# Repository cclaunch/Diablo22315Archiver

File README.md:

Diablo disk drive model 31, in its standard density version, can read or write to the 2315 disk cartridges interchanngeably with the disk drives in the IBM 1130 system 

This project exploits an FPGA board with a custom interface board to control the Diablo disk drive. It will read the contents of the disk cartridge into RAM on the FPGA board. 

It then uploads the contents over the USB serial link so that the contents can be archived. The software will take the data streaming over the USB link and create disk files 
in the format used with the IBM 1130 simulator programs (and therefore with the Virtual 2315 Cartridge Facility to access them on a real 1130 system. 

The PCB connects to the FPGA board, provides power to the FPGA and the logic on the PCB, and connects to the Diablo disk drive using an IDC 50 pin cable.

A PCB is available to create the Head Adapter Tool used in aligning a Diablo 31 standard density drive using the CE Cartridge

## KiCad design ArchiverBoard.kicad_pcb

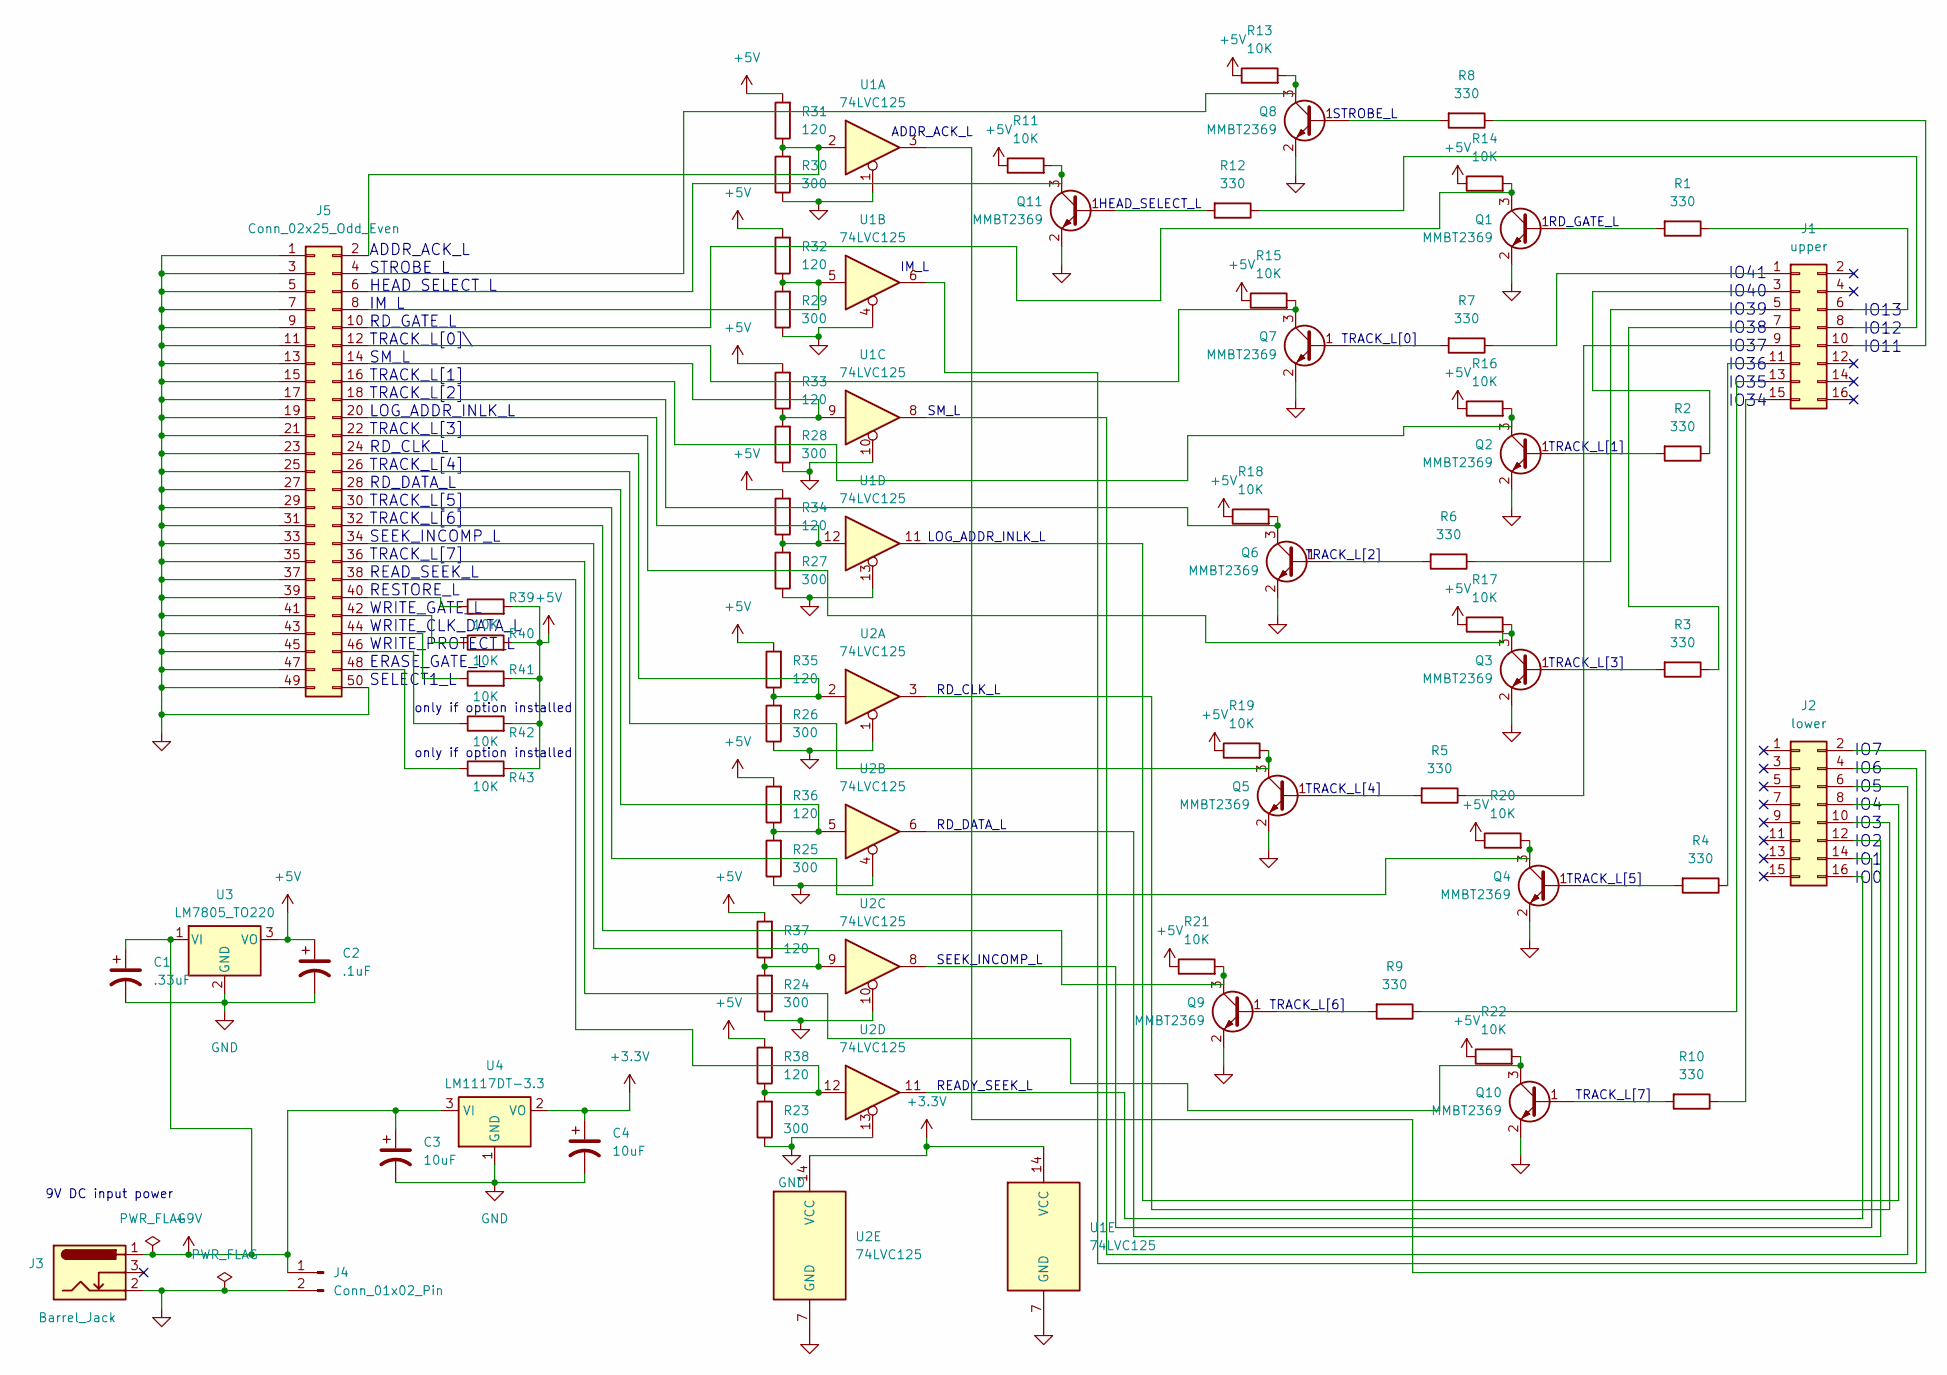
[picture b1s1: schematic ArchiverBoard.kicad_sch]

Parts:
C1: .33uF; C_0805_2012Metric
C2: .1uF; C_1206_3216Metric
C3, C4: 10uF; C_1206_3216Metric
J1: upper; PinHeader_2x08_P2.54mm_Vertical
J2: lower; PinHeader_2x08_P2.54mm_Vertical
J3: Barrel_Jack; BarrelJack_Kycon_KLDX-0202-xC_Horizontal
J4: Conn_01x02_Pin; PinHeader_1x02_P2.54mm_Vertical
J5: Conn_02x25_Odd_Even; IDC-Header_2x25_P2.54mm_Vertical
Q1, Q2, Q3, Q4, Q5, Q6, Q7, Q8, Q9, Q10, Q11: MMBT2369; SOT-23
R1, R2, R3, R4, R5, R6, R7, R8, R9, R10, R12: 330; R_0603_1608Metric
R11, R13, R14, R15, R16, R17, R18, R19, R20, R21, R22, R39, R40, R41, R42, R43: 10K; R_0603_1608Metric
R23, R24, R25, R26, R27, R28, R29, R30: 300; R_0603_1608Metric
R31, R32, R33, R34, R35, R36, R37, R38: 120; R_0603_1608Metric
U1, U2: 74LVC125; SO-14_3.9x8.65mm_P1.27mm
U3: LM7805_TO220; TO-220-3_Vertical
U4: LM1117DT-3.3; SOT-223

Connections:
+3.3V: C4.1, U1.14 (VCC), U2.14 (VCC), U4.2 (VO), U4.4
+5V: C2.1, R11.1, R13.1, R14.1, R15.1, R16.1, R17.1, R18.1, R19.1, R20.1, R21.1, R22.1, R31.2, R32.2, R33.2, R34.2, R35.2, R36.2, R37.2, R38.2, R39.2, R40.2, R41.2, R42.2, R43.2, U3.3 (VO)
+9V: C1.1, C3.1, J3.1, J4.1, U3.1 (VI), U4.3 (VI)
GND: C1.2, C2.2, C3.2, C4.2, J3.2, J4.2, J5.1, J5.3, J5.5, J5.7, J5.9, J5.11, J5.13, J5.15, J5.17, J5.19, J5.21, J5.23, J5.25, J5.27, J5.29, J5.31, J5.33, J5.35, J5.37, J5.39, J5.41, J5.43, J5.45, J5.47, J5.49, J5.50, Q1.2 (E), Q2.2 (E), Q3.2 (E), Q4.2 (E), Q5.2 (E), Q6.2 (E), Q7.2 (E), Q8.2 (E), Q9.2 (E), Q10.2 (E), Q11.2 (E), R23.1, R24.1, R25.1, R26.1, R27.1, R28.1, R29.1, R30.1, U1.1, U1.4, U1.7 (GND), U1.10, U1.13, U2.1, U2.4, U2.7 (GND), U2.10, U2.13, U3.2 (GND), U4.1 (GND)
unnamed: J1.1, R7.1
unnamed: J1.3, R2.1
unnamed: J1.5, R6.1
unnamed: J1.6, R1.1
unnamed: J1.7, R3.1
unnamed: J1.8, R12.1
unnamed: J1.9, R5.1
unnamed: J1.10, R8.1
unnamed: J1.11, R4.1
unnamed: J1.13, R9.1
unnamed: J1.15, R10.1
unnamed: J2.2, U1.3
unnamed: J2.4, U1.6
unnamed: J2.6, U1.8
unnamed: J2.8, U1.11
unnamed: J2.10, U2.3
unnamed: J2.12, U2.6
unnamed: J2.14, U2.8
unnamed: J2.16, U2.11
unnamed: J5.2, R30.2, R31.1, U1.2
unnamed: J5.4, Q8.3 (C), R13.2
unnamed: J5.6, Q11.3 (C), R11.2
unnamed: J5.8, R29.2, R32.1, U1.5
unnamed: J5.10, Q1.3 (C), R14.2
unnamed: J5.12, Q7.3 (C), R15.2
unnamed: J5.14, R28.2, R33.1, U1.9
unnamed: J5.16, Q2.3 (C), R16.2
unnamed: J5.18, Q6.3 (C), R18.2
unnamed: J5.20, R27.2, R34.1, U1.12
unnamed: J5.22, Q3.3 (C), R17.2
unnamed: J5.24, R26.2, R35.1, U2.2
unnamed: J5.26, Q5.3 (C), R19.2
unnamed: J5.28, R25.2, R36.1, U2.5
unnamed: J5.30, Q4.3 (C), R20.2
unnamed: J5.32, Q9.3 (C), R21.2
unnamed: J5.34, R24.2, R37.1, U2.9
unnamed: J5.36, Q10.3 (C), R22.2
unnamed: J5.38, R23.2, R38.1, U2.12
unnamed: J5.40, R39.1
unnamed: J5.42, R40.1
unnamed: J5.44, R41.1
unnamed: J5.46, R42.1
unnamed: J5.48, R43.1
unnamed: Q1.1 (B), R1.2
unnamed: Q2.1 (B), R2.2
unnamed: Q3.1 (B), R3.2
unnamed: Q4.1 (B), R4.2
unnamed: Q5.1 (B), R5.2
unnamed: Q6.1 (B), R6.2
unnamed: Q7.1 (B), R7.2
unnamed: Q8.1 (B), R8.2
unnamed: Q9.1 (B), R9.2
unnamed: Q10.1 (B), R10.2
unnamed: Q11.1 (B), R12.2

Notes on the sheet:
RD_DATA_L
RD_GATE_L
9V DC input power
ADDR_ACK_L STROBE_L HEAD_SELECT_L IM_L RD_GATE_L TRACK_L[0]\ SM_L TRACK_L[1] TRACK_L[2] LOG_ADDR_INLK_L TRACK_L[3] RD_CLK_L TRACK_L[4] RD_DATA_L TRACK_L[5] TRACK_L[6] SEEK_INCOMP_L TRACK_L[7] READ_SEEK_L RESTORE_L WRITE_GATE_L WRITE_CLK_DATA_L WRITE_PROTECT_L ERASE_GATE_L SELECT1_L
IO41 IO40 IO39 IO38 IO37 IO36 IO35 IO34
TRACK_L[7]
ADDR_ACK_L
TRACK_L[2]
TRACK_L[1]
IO13 IO12 IO11
IO7 IO6 IO5 IO4 IO3 IO2 IO1 IO0
LOG_ADDR_INLK_L
TRACK_L[5]
TRACK_L[4]
TRACK_L[6]
READY_SEEK_L
TRACK_L[0]
STROBE_L
SEEK_INCOMP_L
only if option installed
IM_L
HEAD_SELECT_L
RD_CLK_L
TRACK_L[3]
SM_L

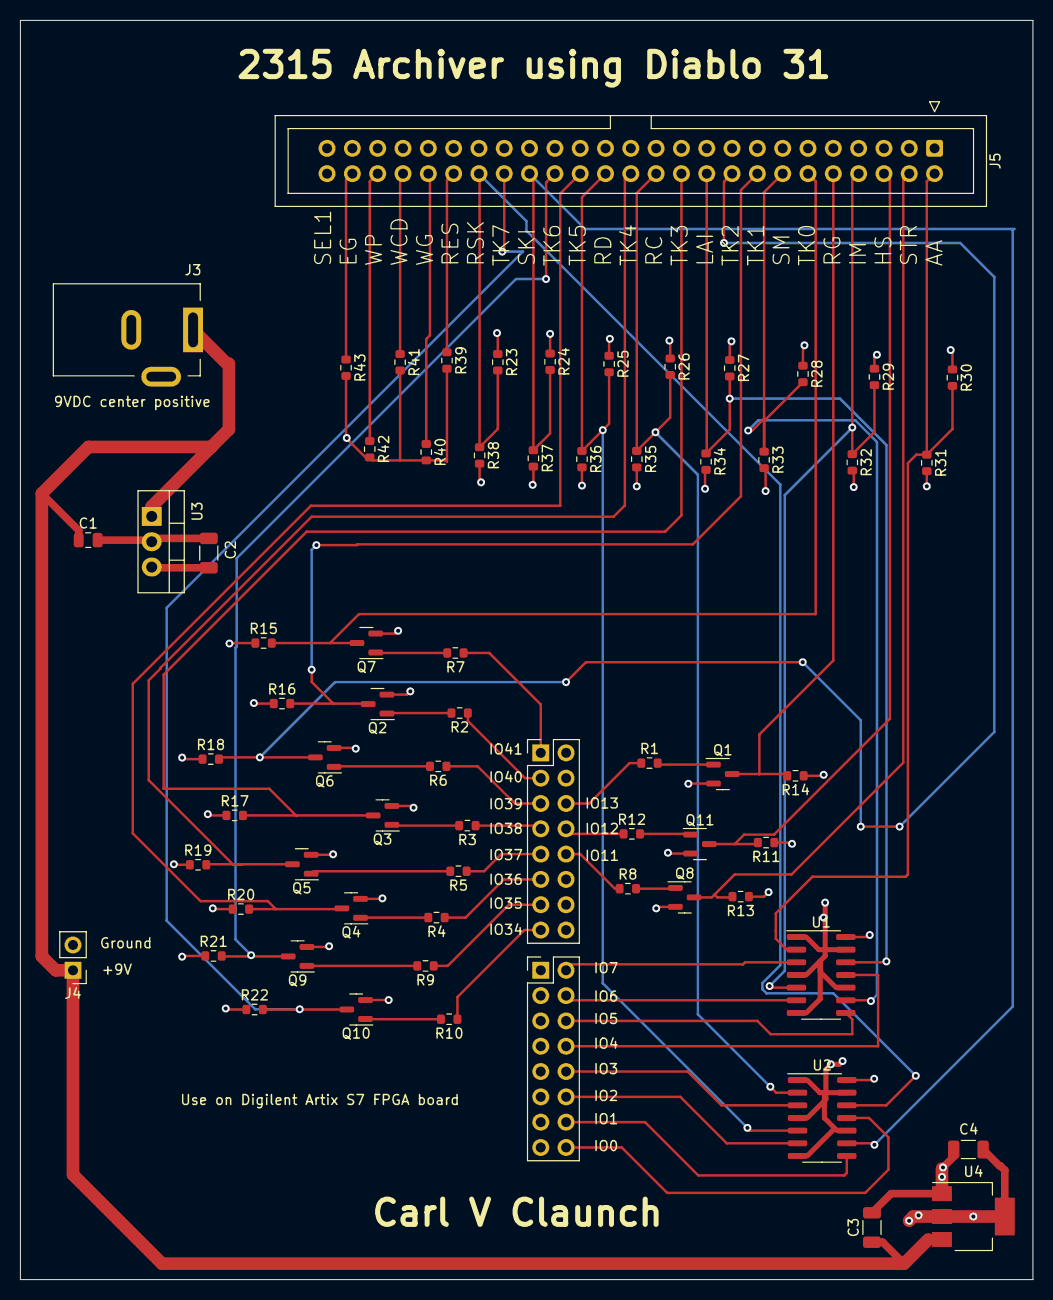
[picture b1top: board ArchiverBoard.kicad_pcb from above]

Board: 4 copper layers, 101.6 x 126.3 mm, 67 parts (0 on the bottom side), 58 nets.

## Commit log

2026-06-23 Create README.md
    Start project
2026-06-23 FPGA files for the archiver logic in the Artix S7 board
2026-06-23 Picture of board from PCBWay.com as it enters production
2026-06-24 Update README.md
    fix typo
2026-06-24 Added bill of materials and PCB files
    Gerbers as well as KiCAD schematic and PCB design
2026-06-24 Updated documentation
    added to signals spreadsheet
    updated theory of operations manual
    updated install and operation manual
2026-06-24 Up to date version of FPGA logic
2026-06-25 SIgnals in PDF format
    spreadsheet of signal assignments
    FPGA, 50 pin connector, MRAC-42 on drive, terminators, direction, etc
2026-06-25 Documentation improvement
    New picture, formatting and arrangement changes
2026-06-25 Updated Bill of Materials
    added items, reformatted, and shared as CSV
2026-06-25 Updated Bill of Matierals
    added items, reformatted, and shared as CSV file
2026-06-30 Added Head Adapter tool and alignment information
    Alignment procedure, special tool to use erase coils for wider null band during alignment, and updated documentation
